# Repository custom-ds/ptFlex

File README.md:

# ptFlex
ptFlex tracker board starting with version 2.0 of the hardware, which is based on the improvements found in the ptSolar tracker. This repo supercedes the original ptFlex-firmware and ptFlex-Hardware repos from the version 1.0 hardware.

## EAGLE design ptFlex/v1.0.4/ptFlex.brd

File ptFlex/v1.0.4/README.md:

# ptFlex v1.0.4

Final version of the 1.0 line of trackers, from the ptFlex-hardware project Repo on Github. The version 2.0 is an evolution of 1.0, but includes a new GPS engine, more readily available GPS antennas, and the circuit has been ported over to KiCad.

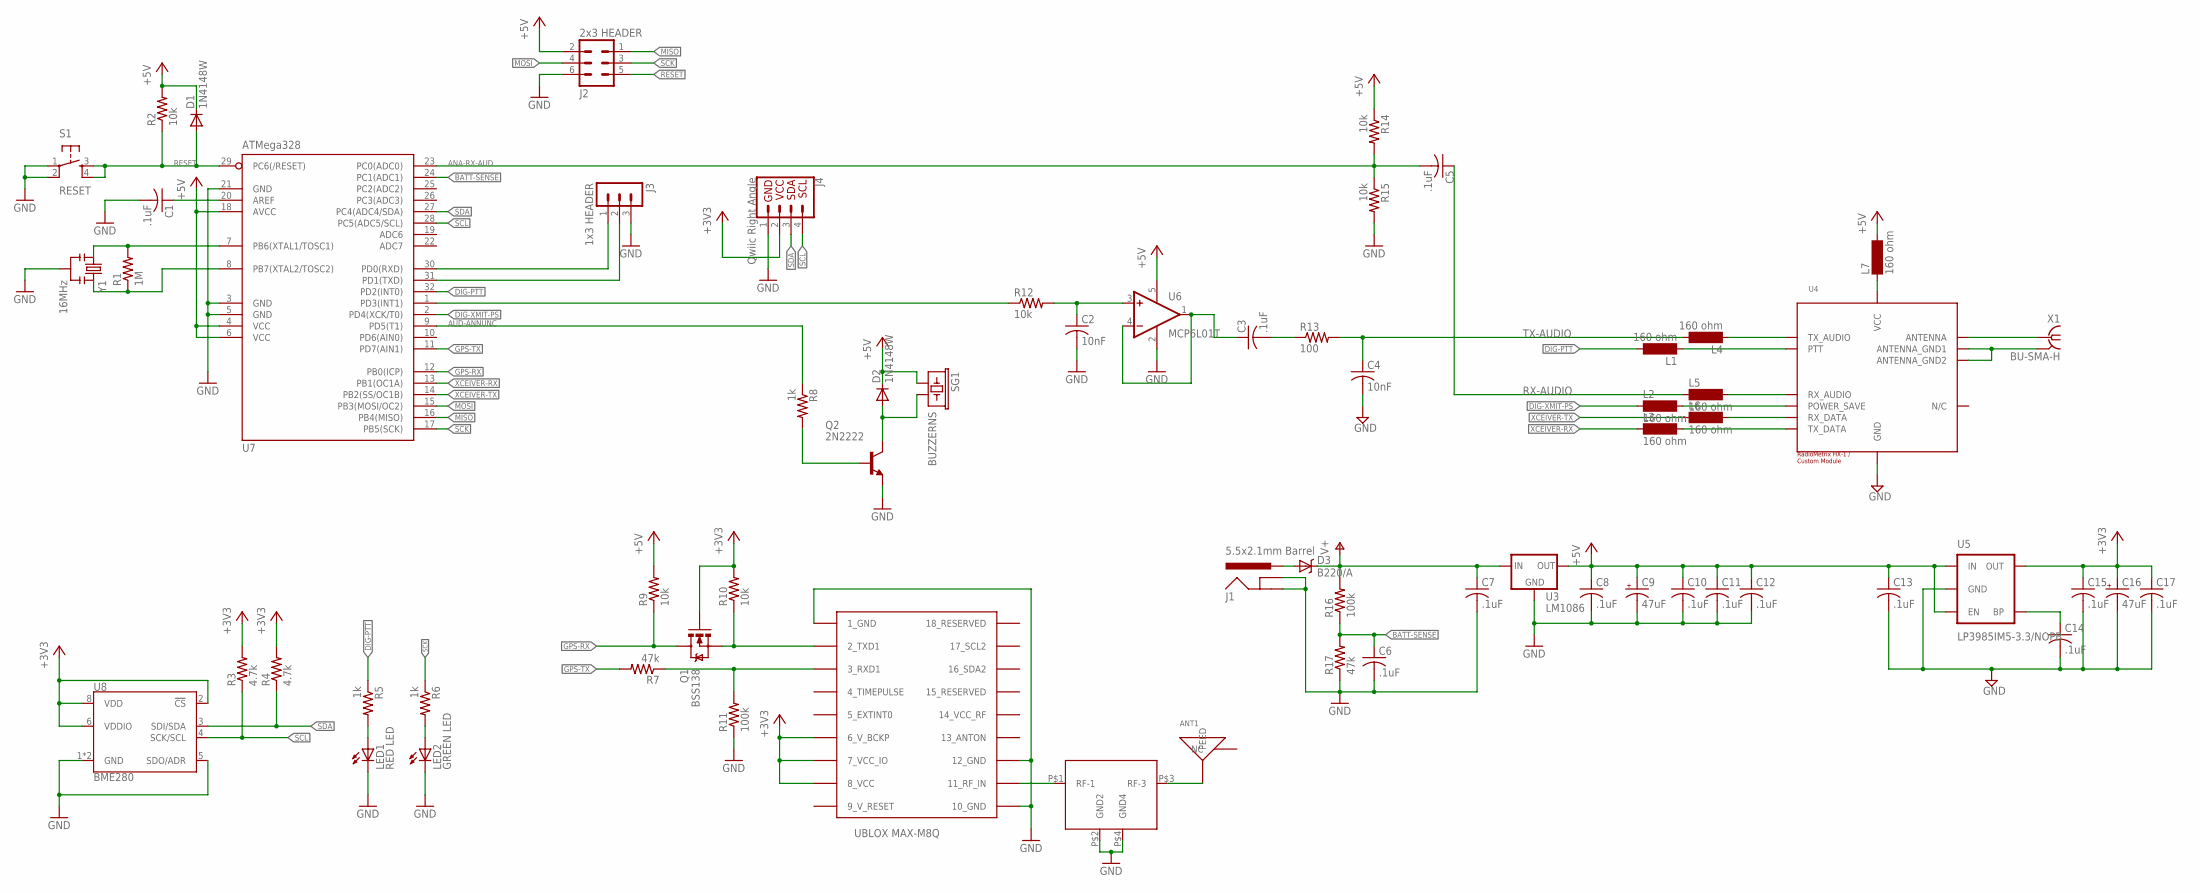
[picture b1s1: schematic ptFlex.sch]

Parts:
ANT1: GPS ANTENNA; 1575AT43A40; DIGIKEY 712-1003-1-ND
C1, C3, C5, C6, C7, C8, C10, C11, C12, C13, C14, C15, C17: .1uF; C0805; DIGIKEY 311-1361-1-ND
C2, C4: 10nF; C0805; DIGIKEY 399-1158-1-ND
C9, C16: 47uF; 153CLV-0605; DIGIKEY PCE3842CT-ND
D1, D2: 1N4148W; SOD123; DIGIKEY 1N4148W-FDICT-ND
D3: B220/A; SMA-DIODE; DIGIKEY 641-1258-1-ND
F1: MURATA-GPS-FILTER; DIGIKEY 583-1198-1-ND
J1: 5.5x2.1mm Barrel; POWER_JACK_SMD; DIGIKEY CP-002AHPJCT-ND
J2: 2x3 HEADER; MA03-2; DIGIKEY 952-2121-ND
J3: 1x3 HEADER; MA03-1; DIGIKEY 952-2264-ND
J4: Qwiic Right Angle; 1X04_1MM_RA; DIGIKEY 455-1804-1-ND
L1, L2, L3, L4, L5, L6, L7: 160 ohm; SM-1206; DIGIKEY 240-2411-1-ND
LED1: RED LED; CHIPLED_1206; DIGIKEY 160-1405-1-ND
LED2: GREEN LED; CHIPLED_1206; DIGIKEY 160-1169-1-ND
Q1: BSS138; SOT23; DIGIKEY BSS138KCT-ND
Q2: 2N2222; SOT23-BEC; DIGIKEY MMBT2222AFSCT-ND
R1: 1M; R0805; DIGIKEY 311-1.0MARCT-ND
R2, R9, R10, R12, R14, R15: 10k; R0805; DIGIKEY 311-10.0KCRCT-ND
R3, R4: 4.7k; R0805; DIGIKEY 311-4.7KARCT-ND
R5, R6, R8: 1k; R0805; DIGIKEY 311-1.0KARCT-ND
R7, R17: 47k; R0805; DIGIKEY 311-47.0KCRCT-ND
R11, R16: 100k; R0805; DIGIKEY 311-100KCRCT-ND
R13: 100; R0805; DIGIKEY 311-100ARCT-ND
S1: RESET; TACTILE_SWITCH_SMD; DIGIKEY CKN9104CT-ND
SG1: BUZZERNS; BUZZER-12MM-NS; DIGIKEY 102-1155-ND
U2: UBLOX_MAX; DIGIKEY 672-1003-1-ND
U3: LM1086; TO263; DIGIKEY LM1086ISX-5.0/NOPBCT-ND
U4: RADIOMETRIX-HX1-CUSTOM
U5: LP3985IM5-3.3/NOPB; SOT23-5; DIGIKEY LP3985IM5-3.3/NOPBCT-ND
U6: MCP6L01T; SOT23-5; DIGIKEY MCP6L01T-E/OTCT-ND
U7: ATMega328; TQFP32-08; DIGIKEY ATMEGA328P-AU-ND
U8: BME280; LGA-8-2.5X2.5; DIGIKEY 828-1063-1-ND
X1: BU-SMA-H; DIGIKEY CONSMA001-ND
Y1: 16MHz; RESONATOR-SMD; DIGIKEY 478-5420-1-ND

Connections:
9_V_RESET: U2.9_V_RESET
+3V3: C15.1, C16.+, C17.1, J4.2, Q1.1 (G), R3.2, R4.2, R10.2, U2.6_V_BCKP, U2.7_VCC_IO, U2.8_VCC, U5.5 (OUT), U8.2 (!CS), U8.6 (VDDIO), U8.8 (VDD)
+5V: C8.1, C9.+, C10.1, C11.1, C12.1, C13.1, D1.C, D2.C, J2.2, L7.2, R2.2, R9.2, R14.1, SG1.+ (1), U3.2 (OUT), U5.1 (IN), U5.3 (EN), U6.5 (V+), U7.4 (VCC), U7.6 (VCC), U7.18 (AVCC)
ANA-RX-AUD: C5.2, R14.2, R15.1, U7.23 (PC0(ADC0))
AUD-ANNUNC: R8.1, U7.9 (PD5(T1))
BATT-SENSE: C6.1, R16.1, R17.2, U7.24 (PC1(ADC1))
DIG-PTT: L1.2, R5.1, U7.32 (PD2(INT0))
DIG-XMIT-PS: L2.1, U7.2 (PD4(XCK/T0))
GND: C1.2, C2.2, C4.2, C6.2, C7.2, C8.2, C9.-, C10.2, C11.2, C12.2, C13.2, C14.2, C15.2, C16.-, C17.2, F1.P$2 (GND2), F1.P$4 (GND4), J1.GND (GNDBREAK), J1.P$4 (GND), J2.6, J3.3, J4.1, LED1.C, LED2.C, Q2.E, R11.1, R15.2, R17.1, S1.1, S1.2, U2.1_GND, U2.10_GND, U2.12_GND, U3.1 (GND), U4.GND, U5.2 (GND), U6.2 (V-), U7.3 (GND), U7.5 (GND), U7.21 (GND), U8.1 (GND), U8.5 (SDO/ADR), U8.7 (GND), Y1.2
GPS-RX: Q1.3 (D), R9.1, U7.12 (PB0(ICP))
GPS-TX: R7.2, U7.11 (PD7(AIN1))
MISO: J2.1, U7.16 (PB4(MISO))
MOSI: J2.4, U7.15 (PB3(MOSI/OC2))
unnamed: C2.1, R12.2, U6.3 (+IN)
unnamed: F1.P$1 (RF-1), U2.11_RF_IN
unnamed: ANT1.FEED, F1.P$3 (RF-3)
unnamed: U4.ANTENNA, X1.1
unnamed: L4.1, U4.TX_AUDIO
unnamed: L1.1, U4.PTT
unnamed: D3.A, J1.VIN0 (PWR)
unnamed: D2.A, Q2.C, SG1.- (2)
unnamed: C4.1, L4.2, R13.2
unnamed: C3.1, U6.1 (OUT), U6.4 (-IN)
unnamed: L5.2, U4.RX_AUDIO
unnamed: R12.1, U7.1 (PD3(INT1))
unnamed: L2.2, U4.POWER_SAVE
unnamed: Q1.2 (S), R10.1, U2.2_TXD1
unnamed: R1.1, U7.8 (PB7(XTAL2/TOSC2)), Y1.3
unnamed: R7.1, R11.2, U2.3_RXD1
unnamed: L6.2, U4.RX_DATA
unnamed: L3.2, U4.TX_DATA
unnamed: LED1.A, R5.2
unnamed: LED2.A, R6.2
unnamed: Q2.B, R8.2
unnamed: C1.1, U7.20 (AREF)
unnamed: C14.1, U5.4 (BP)
unnamed: R1.2, U7.7 (PB6(XTAL1/TOSC1)), Y1.1
RESET: D1.A, J2.5, R2.1, S1.3, S1.4, U7.29 (PC6(/RESET))
RFGND: U4.ANTENNA_GND1, U4.ANTENNA_GND2, X1.2, X1.3 (2), X1.4 (2), X1.5 (2)
RX-AUDIO: C5.1, L5.1
RXD: J3.1, U7.30 (PD0(RXD))
SCK: J2.3, R6.1, U7.17 (PB5(SCK))
SCL: J4.4, R3.1, U7.28 (PC5(ADC5/SCL)), U8.4 (SCK/SCL)
SDA: J4.3, R4.1, U7.27 (PC4(ADC4/SDA)), U8.3 (SDI/SDA)
TX-AUDIO: C3.2, R13.1
TXD: J3.2, U7.31 (PD1(TXD))
V+: C7.1, D3.C, R16.2, U3.3 (IN)
VCC: L7.1, U4.VCC
XCEIVER-RX: L3.1, U7.13 (PB1(OC1A))
XCEIVER-TX: L6.1, U7.14 (PB2(SS/OC1B))

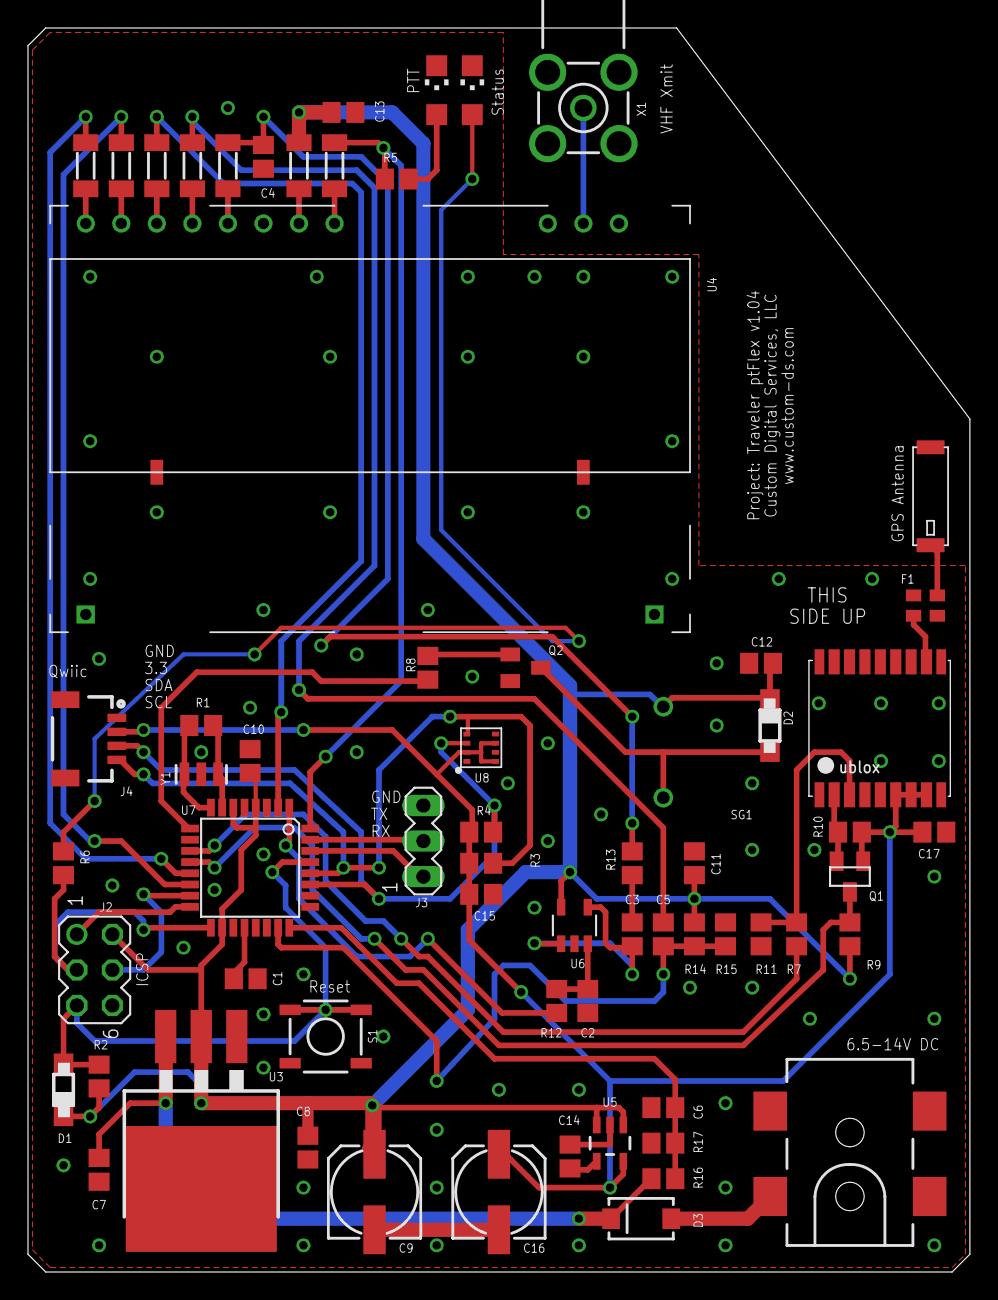
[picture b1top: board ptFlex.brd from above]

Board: 2 copper layers, 67.3 x 88.9 mm, 65 parts (0 on the bottom side), 49 nets.

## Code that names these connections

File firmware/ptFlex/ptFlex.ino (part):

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#include "SparkFunBME280.h"
#include <Wire.h>

//PD0 is Serial Port RX
//PD1 is Serial Port TX
#define PIN_PTT_OUT 2     //PD2
#define PIN_AUDIO_OUT 3   //PD3   - APRS Packet Audio
#define PIN_DRA_EN 4      //PD4
#define PIN_AUDIO 5       //PD5   - Audio Annunciation
#define PIN_GPS_EN 6      //PD6
#define PIN_GPS_TX 7      //PD7

#define PIN_GPS_RX 8      //PB0
#define PIN_DRA_TX 9      //PB1
#define PIN_DRA_RX 10     //PB2
//PB3 is MOSI
//PB4 is MISO
#define PIN_LED 13        //PB5

//Analog Pins
#define PIN_AUDIO_IN A0   //PC0
#define PIN_ANALOG_BATTERY A1   //PC1
//PC2 is not used
//PC3 is not used
//PC4 is SDA
//PC5 is SCL
//PC6 is reset and not available


#define DELAY_MS_BETWEEN_XMITS 1250   //How many MS to delay between subsequent packets (as in between GPGGA and GPRMC strings
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      break;
  }
  
  OCR2B = Aprs.getDACValue(highByte(iTonePhase));   //analogWrite to PIN PD3, directly using the OCR register

  iRateGen--;
  if (iRateGen == 0) {
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
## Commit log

2025-06-15 Initial transfer of ptSolar to ptFlex starter files.
2025-06-21 Schematic mostly revised for v2.0
2025-06-21 PCB nearing final
2025-06-22 Back filed old versions of PCB from the ptFlex-hardware project into this repo. Shrunk the PCB down by 5mm.
2025-06-22 Swapped out Piezo symbol. Minor tweaks
2025-06-22 Renumbered all parts.
2025-06-24 Finalized version 2.0.0 of the PCB to bring it in sync with the ptSolar design.
2025-07-11 Migrated firmware from ptSolar to ptFlex. Adjusting for new defaults, 16MHz clock speed, and voltage sense divider change.
2025-07-12 Updated to firmware 1.5.0. This includes a few minor fixes, and an update to configuration version PT0101. Backwards support for alternate GPS and transmitters has been removed.
2025-07-19 Board redesigned to 2.0.1 to fix missing SDA/SCL pins to uC. Shrunk board slightly. Fixed SMA center hole being too small.
2025-07-21 Version 1.5.1 syncs up the libraries between ptFlex and ptSolar.
2025-07-29 Firmware 1.5.2. Added feature to adjust path when transmitting on ISS frequency.
2025-07-29 Adjusting voltage divider resistor precision.
2025-08-22 Updating to PCB 2.0.1 to fix missing I2C wires.
2025-09-26 Updates synced for 1.6
2025-09-27 Adjusting for cold-weather operation.
2025-09-27 General clean up
2025-09-27 Adjusting gitignore
2026-04-12 Finalizing PCB v2.0.2. Including some minor tweaks to the firmware as well.
2026-04-20 Adjusting to better defaults in the firmware's configuration.
2026-04-21 Updated to firmware 1.6.1. Simplified test tools to function with ptConfigurator.
2026-05-18 Updated BOM parts
2026-05-18 Added logic to handle invalid gps fix.
2026-05-31 Limiting GPS debug noise
2026-05-31 Fix for GPS Delay being out of order in config strings
2026-06-09 Better debug output when handling GPS delays.
2026-06-09 Replaced missing files

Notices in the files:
firmware/ptFlex/ptFlex.ino:
Copyright 2011-2026 - Zack Clobes (W0ZC), Custom Digital Services, LLC
This program is free software: you can redistribute it and/or modify it under the terms of the GNU General Public License as published by
the Free Software Foundation, either version 3 of the License, or (at your option) any later version.
parts and their libraries:
SparkFun-FreqCtrl: Licensing: CC v3.0 Share-Alike You are welcome to use this library for commercial purposes.
